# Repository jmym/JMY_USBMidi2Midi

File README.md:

# JMY_USBMidi2Midi
An USB midi Converter to a midi USB

You could connect two PC's, two MAC's, one PC and one Mac, one PC and one Raspberry pi, etc., By USB ports

Como microcontrolador he usado la placa de Arduino Seeeduino XIAO.

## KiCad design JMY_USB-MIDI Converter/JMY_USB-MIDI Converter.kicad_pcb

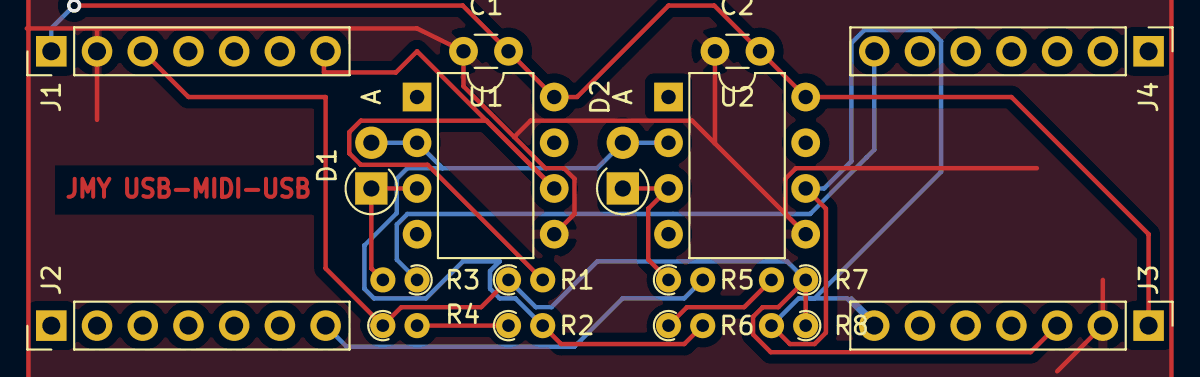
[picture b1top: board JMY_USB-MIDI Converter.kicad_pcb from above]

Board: 2 copper layers, 18 parts (0 on the bottom side), 12 nets.

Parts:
C1, C2: 100nF; C_Disc_D3.0mm_W1.6mm_P2.50mm
D1, D2: DIODE; D_A-405_P2.54mm_Vertical_AnodeUp
J1, J2, J3, J4: Conn_01x07_Male; PinHeader_1x07_P2.54mm_Vertical
R1: 470R; R_Axial_DIN0204_L3.6mm_D1.6mm_P1.90mm_Vertical
R2, R6: 220; R_Axial_DIN0204_L3.6mm_D1.6mm_P1.90mm_Vertical
R3, R4, R5, R7: 47; R_Axial_DIN0204_L3.6mm_D1.6mm_P1.90mm_Vertical
R8: 470; R_Axial_DIN0204_L3.6mm_D1.6mm_P1.90mm_Vertical
U1, U2: 6N138; DIP-8_W7.62mm

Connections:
+3V3: J1.3, J3.3, R1.1, R3.1, R7.1, R8.1
+5V: C1.1, C2.1, J1.1, J3.1, U1.8, U2.8
GND: C1.2, C2.2, J1.2, J3.2, U1.5, U2.5
unnamed: D1.1, R4.2, U1.3
unnamed: D1.2, D2.2, R2.2, R6.2, U1.2, U2.2
unnamed: D2.1, R5.1, U2.3
unnamed: J1.7, R1.2, U1.6
unnamed: J2.7, R5.2
unnamed: J3.7, R8.2, U2.6
unnamed: J4.7, R4.1
unnamed: R2.1, R3.2
unnamed: R6.1, R7.2
